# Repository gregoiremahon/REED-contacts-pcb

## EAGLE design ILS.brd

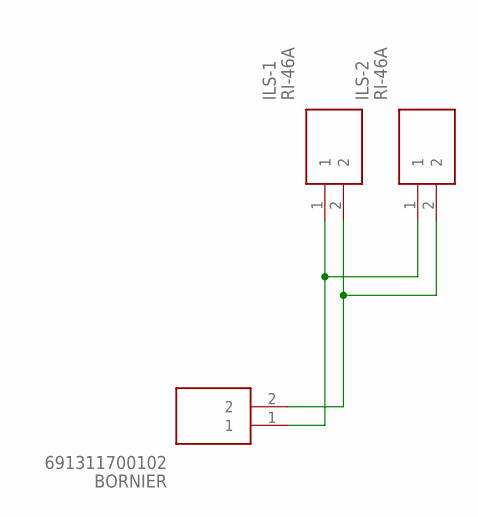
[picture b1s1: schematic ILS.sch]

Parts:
BORNIER: 691311700102; SHDR2W100P0X500_1X2_1200X850X1
ILS-1, ILS-2: RI-46A; RESAD3130W65L2050D270

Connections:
unnamed: BORNIER.1, ILS-1.1, ILS-2.1
unnamed: BORNIER.2, ILS-1.2, ILS-2.2

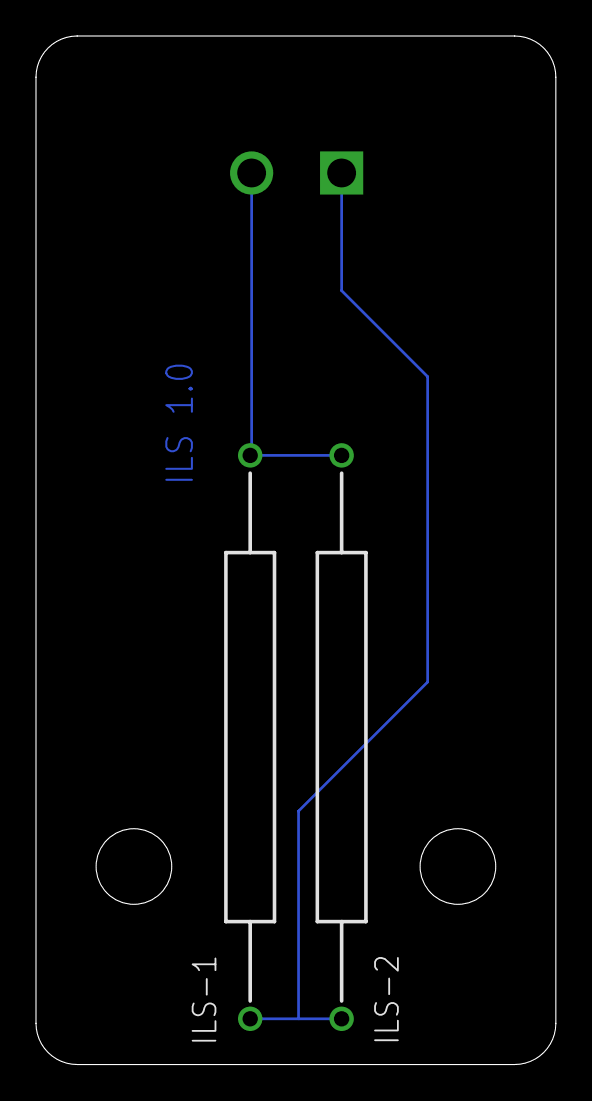
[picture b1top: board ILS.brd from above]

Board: 2 copper layers, 28.9 x 57.1 mm, 3 parts (1 on the bottom side), 2 nets.

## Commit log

2022-03-02 main files
